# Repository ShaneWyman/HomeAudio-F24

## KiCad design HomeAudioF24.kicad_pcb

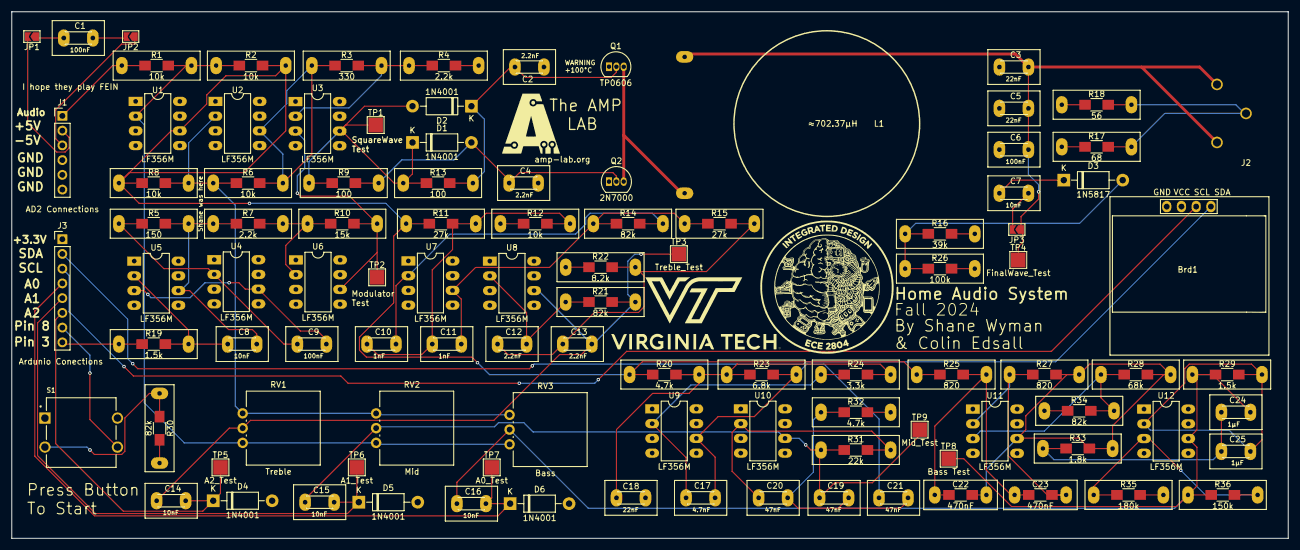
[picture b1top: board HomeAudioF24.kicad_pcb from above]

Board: 4 copper layers, 220.0 x 90.8 mm, 102 parts (0 on the bottom side), 55 nets.

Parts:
Brd1: SSD1306; 128x64OLED SSD1306
C1, C6, C9: 100nF; C_Disc_D4.3mm_W1.9mm_P5.00mm_Handsolder
C2, C4, C12, C13: 2.2nF; C_Disc_D4.3mm_W1.9mm_P5.00mm_Handsolder
C3, C5, C18: 22nF; C_Disc_D4.3mm_W1.9mm_P5.00mm_Handsolder
C7, C8, C14, C15, C16: 10nF; C_Disc_D4.3mm_W1.9mm_P5.00mm_Handsolder
C10, C11: 1nF; C_Disc_D4.3mm_W1.9mm_P5.00mm_Handsolder
C17: 4.7nF; C_Disc_D4.3mm_W1.9mm_P5.00mm_Handsolder
C19, C20, C21: 47nF; C_Disc_D4.3mm_W1.9mm_P5.00mm_Handsolder
C22, C23: 470nF; R_Combo
C24, C25: 1μF; C_Disc_D4.3mm_W1.9mm_P5.00mm_Handsolder
D1, D2, D4, D5, D6: 1N4001; D_DO-41_SOD81_P10.16mm_Horizontal
D3: 1N5817; D_DO-41_SOD81_P10.16mm_Horizontal
J1: AD2 Connections; PinHeader_1x06_P2.54mm_Vertical
J2: AudioJack2_Ground; Jack_3.5mm_Ground_RightAngle
J3: Ardunio Conections; PinHeader_1x08_P2.54mm_Vertical
JP1, JP2, JP3: SolderJumper_2_Open; SolderJumper-2_P1.3mm_Open_TrianglePad1.0x1.5mm
L1: ≈702.37μH; InductorCore
Q1: TP0606; TO-92L_Inline
Q2: 2N7000; TO-92_Inline
R1, R2, R6, R8, R12: 10k; 1_2W Res + 1206
R3: 330; 1_2W Res + 1206
R4, R7: 2.2k; 1_2W Res + 1206
R5: 150; 1_2W Res + 1206
R9, R13: 100; 1_2W Res + 1206
R10: 15k; 1_2W Res + 1206
R11, R15: 27k; 1_2W Res + 1206
R14, R21, R30, R34: 82k; 1_2W Res + 1206
R16: 39k; 1_2W Res + 1206
R17: 68; 1_2W Res + 1206
R18: 56; 1_2W Res + 1206
R19, R29: 1.5k; 1_2W Res + 1206
R20, R32: 4.7k; 1_2W Res + 1206
R22: 8.2k; 1_2W Res + 1206
R23: 6.8k; 1_2W Res + 1206
R24: 3.3k; 1_2W Res + 1206
R25, R27: 820; 1_2W Res + 1206
R26: 100k; 1_2W Res + 1206
R28: 68k; 1_2W Res + 1206
R31: 22k; 1_2W Res + 1206
R33: 1.8k; 1_2W Res + 1206
R35: 180k; 1_2W Res + 1206
R36: 150k; 1_2W Res + 1206
RV1: Treble; Potentiometer_Vishay_148-149_Single_Vertical
RV2: Mid; Potentiometer_Vishay_148-149_Single_Vertical
RV3: Bass; Potentiometer_Vishay_148-149_Single_Vertical
S1: VS-1213-67-160GF; SW_VS-1213-67-160GF
TP1: SquareWave_Test; TestPoint_Pad_2.5x2.5mm
TP2: Modulator_test; TestPoint_Pad_2.5x2.5mm
TP3: Treble_Test; TestPoint_Pad_2.5x2.5mm
TP4: FinalWave_Test; TestPoint_Pad_2.5x2.5mm
TP5: A2_Test; TestPoint_Pad_2.5x2.5mm
TP6: A1_Test; TestPoint_Pad_2.5x2.5mm
TP7: A0_Test; TestPoint_Pad_2.5x2.5mm
TP8: Bass Test; TestPoint_Pad_2.5x2.5mm
TP9: Mid_Test; TestPoint_Pad_2.5x2.5mm
U1, U2, U3, U4, U5, U6, U7, U8, U9, U10, U11, U12: LF356M; DIP-8_W7.62mm_LongPads

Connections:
+3.3V: Brd1.2 (VCC), D4.2 (A), D5.2 (A), D6.2 (A), J3.1, S1.1
+5V: J1.2, JP1.2 (B), Q1.1 (S), R26.2, U1.7 (V+), U2.7 (V+), U3.7 (V+), U4.7 (V+), U5.7 (V+), U6.7 (V+), U7.7 (V+), U8.7 (V+), U9.7 (V+), U10.7 (V+), U11.7 (V+), U12.7 (V+)
-5V: J1.3, JP2.1 (A), Q2.1 (S), U1.4 (V-), U2.4 (V-), U3.4 (V-), U4.4 (V-), U5.4 (V-), U6.4 (V-), U7.4 (V-), U8.4 (V-), U9.4 (V-), U10.4 (V-), U11.4 (V-), U12.4 (V-)
A0: C16.2, D6.1 (K), J3.4, TP7.1
A1: C15.2, D5.1 (K), J3.5, TP6.1
A2: C14.2, D4.1 (K), J3.6, TP5.1
Audio_In: J1.1, R1.1
Bass_In: R2.2, R8.1, R11.1, R20.1, R25.1, U1.6 (OUT)
Bass_Out: C16.1, C24.2, R29.1, R36.1, RV3.2, TP8.1, U12.6 (OUT)
Button_Pin: J3.7, S1.4
Filters_Out: R3.1, R6.2, U2.6 (OUT)
GND: Brd1.1 (GND), C2.1, C3.1, C4.2, C5.1, C6.1, C18.2, J1.4, J1.5, J1.6, R4.2, R12.1, R16.2, R17.1, R18.1, R22.1, R30.2, R32.2, R34.1, R35.2, U1.3 (+IN), U2.3 (+IN), U4.3 (+IN), U6.3 (+IN), U7.3 (+IN), U8.3 (+IN), U9.3 (+IN), U10.3 (+IN)
Mid_Out: C15.1, C19.1, R31.1, RV2.2, TP9.1, U10.6 (OUT)
Modulator_In: J3.8, R19.1
Modulator_Out: R10.2, TP2.1, U3.3 (+IN), U6.6 (OUT)
unnamed: C10.1, C11.1, R11.2, R12.2
unnamed: C12.1, C13.1, R15.2, R22.2
unnamed: C18.1, R20.2, R23.1, R24.2
unnamed: C19.2, C20.2, C21.2, R32.1
unnamed: C22.1, C23.1, R25.2
unnamed: C24.1, C25.1, R33.1
unnamed: D1.1 (K), D2.2 (A), R9.1, R13.1, TP1.1, U3.6 (OUT)
unnamed: C2.2, D2.1 (K), Q1.2 (G), R13.2
unnamed: C4.1, D1.2 (A), Q2.2 (G), R9.2
unnamed: D3.2 (A), R16.1, R26.1
unnamed: C7.1, D3.1 (K)
unnamed: J2.G, R17.2, R18.2
unnamed: C3.2, C5.2, C6.2, J2.S, J2.T, JP3.1 (A), L1.2, TP4.1
unnamed: C7.2, JP3.2 (B)
unnamed: C1.1, JP1.1 (A)
unnamed: C1.2, JP2.2 (B)
unnamed: L1.1, Q1.3 (D), Q2.3 (D)
unnamed: R30.1, S1.2
unnamed: C9.2, U4.6 (OUT), U5.3 (+IN)
unnamed: C8.1, R19.2, U5.2 (-IN)
unnamed: C8.2, R5.2, R7.1, U5.6 (OUT)
unnamed: C9.1, R5.1, U4.2 (-IN)
unnamed: R7.2, R10.1, U6.2 (-IN)
unnamed: R1.2, R2.1, RV1.1, RV2.1, RV3.1, U1.2 (-IN)
unnamed: R6.1, R8.2, RV1.3, RV2.3, RV3.3, U2.2 (-IN)
unnamed: C10.2, R14.2, U7.2 (-IN)
unnamed: C11.2, R14.1, R15.1, U7.6 (OUT)
unnamed: C12.2, R21.1, U8.2 (-IN)
unnamed: C17.1, R24.1, U9.2 (-IN)
unnamed: C17.2, C21.1, R23.2, U9.6 (OUT)
unnamed: C20.1, R31.2, U10.2 (-IN)
unnamed: R28.1, R34.2, U11.3 (+IN)
unnamed: C23.2, R27.1, U11.2 (-IN)
unnamed: C22.2, R27.2, R28.2, R33.2, U11.6 (OUT)
unnamed: R35.1, R36.2, U12.3 (+IN)
unnamed: C25.2, R29.2, U12.2 (-IN)
unnamed: R3.2, R4.1, U3.2 (-IN)
SCL: Brd1.3 (SCL), J3.3
SDA: Brd1.4 (SDA), J3.2
Treble_Out: C13.2, C14.1, R21.2, RV1.2, TP3.1, U8.6 (OUT)

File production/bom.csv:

Designator,Footprint,Quantity,Value,LCSC Part #
BRD1,128x64OLED  SSD1306,1,SSD1306,
"C1, C6, C9",C_Disc_D4.3mm_W1.9mm_P5.00mm_Handsolder,3,100nF,
"C10, C11",C_Disc_D4.3mm_W1.9mm_P5.00mm_Handsolder,2,1nF,
"C12, C13, C2, C4",C_Disc_D4.3mm_W1.9mm_P5.00mm_Handsolder,4,2.2nF,
"C14, C15, C16, C7, C8",C_Disc_D4.3mm_W1.9mm_P5.00mm_Handsolder,5,10nF,
C17,C_Disc_D4.3mm_W1.9mm_P5.00mm_Handsolder,1,4.7nF,
"C18, C3, C5",C_Disc_D4.3mm_W1.9mm_P5.00mm_Handsolder,3,22nF,
"C19, C20, C21",C_Disc_D4.3mm_W1.9mm_P5.00mm_Handsolder,3,47nF,
"C22, C23",R_Combo,2,470nF,
"C24, C25",C_Disc_D4.3mm_W1.9mm_P5.00mm_Handsolder,2,1μF,
"D1, D2, D4, D5, D6",D_DO-41_SOD81_P10.16mm_Horizontal,5,1N4001,
D3,D_DO-41_SOD81_P10.16mm_Horizontal,1,1N5817,
J1,PinHeader_1x06_P2.54mm_Vertical,1,AD2 Connections,
J2,Jack_3.5mm_Ground_RightAngle,1,AudioJack2_Ground,
J3,PinHeader_1x08_P2.54mm_Vertical,1,Ardunio Conections,
L1,InductorCore,1,≈702.37μH,
Q1,TO-92L_Inline,1,TP0606,
Q2,TO-92_Inline,1,2N7000,
"R1, R12, R2, R6, R8",1_2W Res + 1206,5,10k,
R10,1_2W Res + 1206,1,15k,
"R11, R15",1_2W Res + 1206,2,27k,
"R13, R9",1_2W Res + 1206,2,100,
"R14, R21, R30, R34",1_2W Res + 1206,4,82k,
R16,1_2W Res + 1206,1,39k,
R17,1_2W Res + 1206,1,68,
R18,1_2W Res + 1206,1,56,
"R19, R29",1_2W Res + 1206,2,1.5k,
"R20, R32",1_2W Res + 1206,2,4.7k,
R22,1_2W Res + 1206,1,8.2k,
R23,1_2W Res + 1206,1,6.8k,
R24,1_2W Res + 1206,1,3.3k,
"R25, R27",1_2W Res + 1206,2,820,
R26,1_2W Res + 1206,1,100k,
R28,1_2W Res + 1206,1,68k,
R3,1_2W Res + 1206,1,330,
R31,1_2W Res + 1206,1,22k,
R33,1_2W Res + 1206,1,1.8k,
R35,1_2W Res + 1206,1,180k,
R36,1_2W Res + 1206,1,150k,
"R4, R7",1_2W Res + 1206,2,2.2k,
R5,1_2W Res + 1206,1,150,
RV1,Potentiometer_Vishay_148-149_Single_Vertical,1,Treble,
RV2,Potentiometer_Vishay_148-149_Single_Vertical,1,Mid,
RV3,Potentiometer_Vishay_148-149_Single_Vertical,1,Bass,
S1,SW_VS-1213-67-160GF,1,VS-1213-67-160GF,
TP1,TestPoint_Pad_2.5x2.5mm,1,SquareWave_Test,
TP2,TestPoint_Pad_2.5x2.5mm,1,Modulator_test,
TP3,TestPoint_Pad_2.5x2.5mm,1,Treble_Test,
TP4,TestPoint_Pad_2.5x2.5mm,1,FinalWave_Test,
TP5,TestPoint_Pad_2.5x2.5mm,1,A2_Test,
TP6,TestPoint_Pad_2.5x2.5mm,1,A1_Test,
TP7,TestPoint_Pad_2.5x2.5mm,1,A0_Test,
TP8,TestPoint_Pad_2.5x2.5mm,1,Bass Test,
TP9,TestPoint_Pad_2.5x2.5mm,1,Mid_Test,
"U1, U10, U11, U12, U2, U3, U4, U5, U6, U7, U8, U9",DIP-8_W7.62mm_LongPads,12,LF356M,

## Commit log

2024-11-21 Initial Git Push
    pain 24/7
2024-11-24 First Major Revision
2024-11-24 Compact version done
2024-11-24 fixed Audio footprint
2024-11-24 Fixed some silkscreens
2024-11-24 Added production Folder
2024-11-25 Fixed another silkscreen
2024-11-25 Added 2 logos, fixed some traces
